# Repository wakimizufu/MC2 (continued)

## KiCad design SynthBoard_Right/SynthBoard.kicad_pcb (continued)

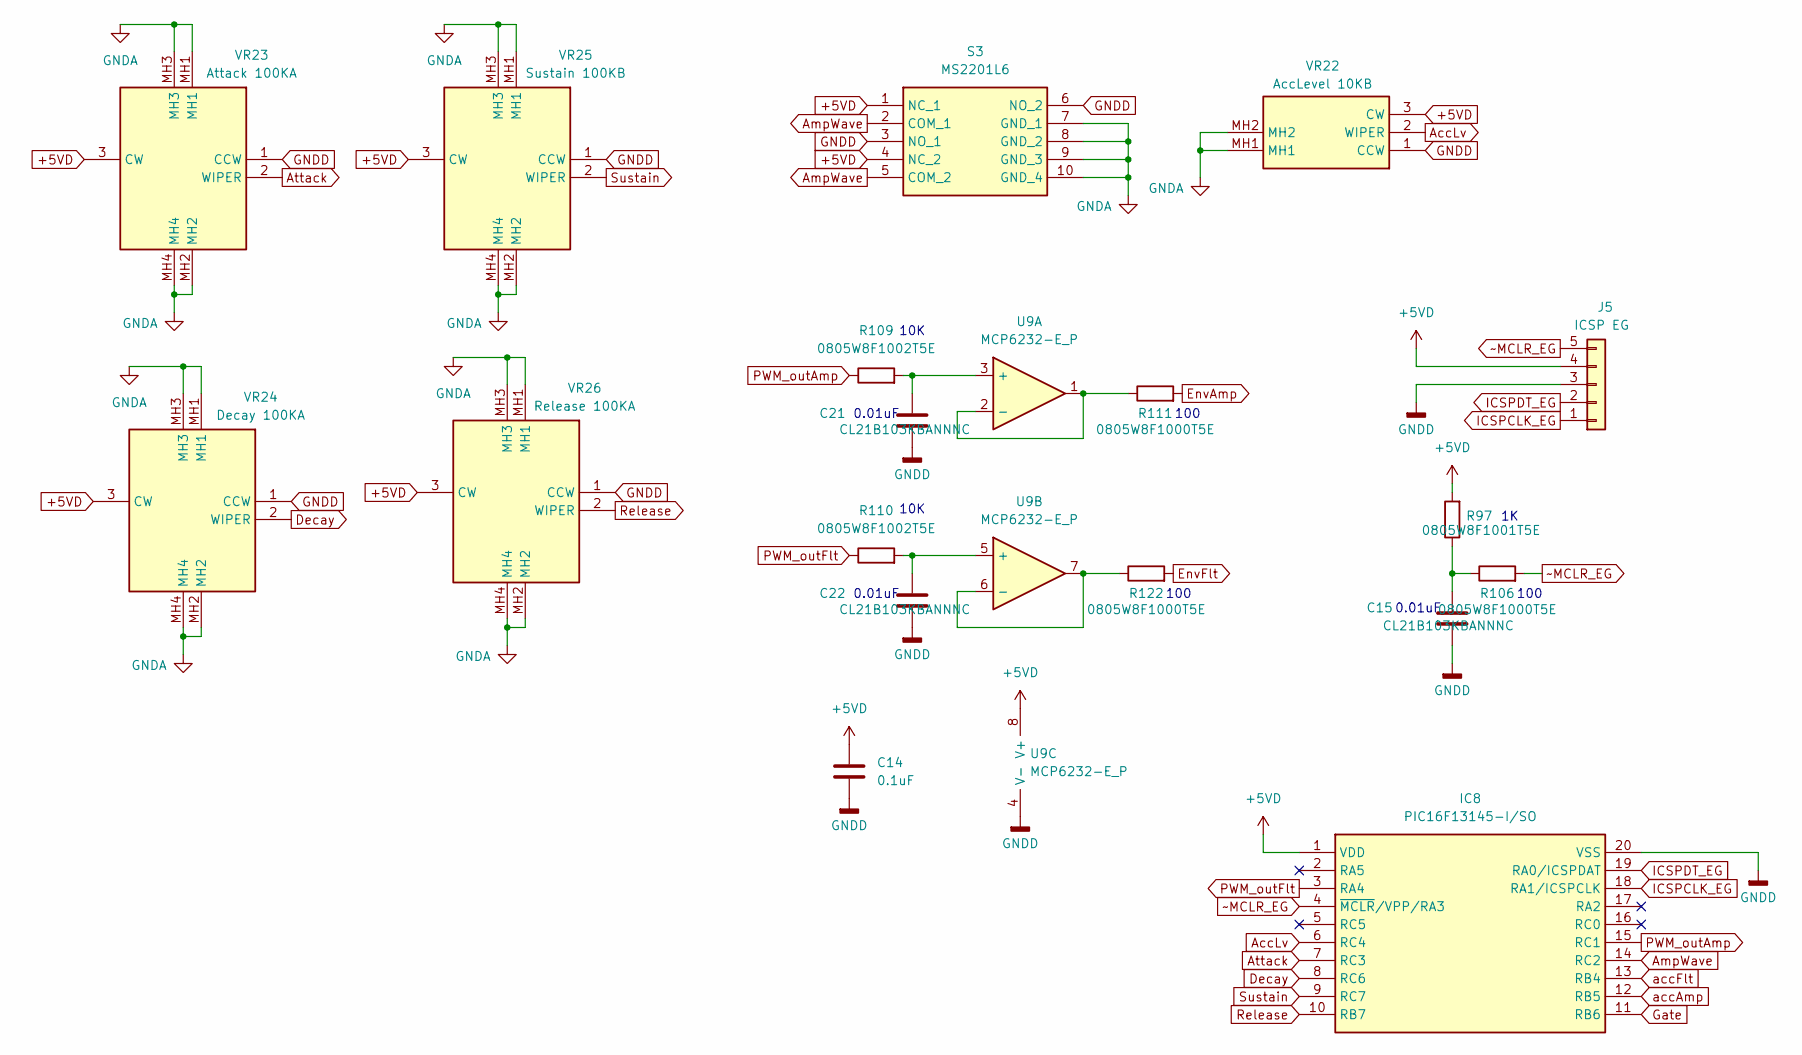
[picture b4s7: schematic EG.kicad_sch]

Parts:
C14: 0.1uF; C_0805_2012Metric_Pad1.18x1.45mm_HandSolder
C15, C21, C22: CL21B103KBANNNC; C_0805_2012Metric_Pad1.18x1.45mm_HandSolder
IC8: PIC16F13145-I/SO; SOIC-20W_7.5x12.8mm_P1.27mm; Manufacturer_Part_Number PIC16F13145-I/P; Mouser Part Number 579-PIC16F13145-I/P
J5: ICSP EG; PinHeader_1x05_P2.54mm_Vertical
R97: 0805W8F1001T5E; R_0805_2012Metric_Pad1.20x1.40mm_HandSolder
R106, R111, R122: 0805W8F1000T5E; R_0805_2012Metric_Pad1.20x1.40mm_HandSolder
R109, R110: 0805W8F1002T5E; R_0805_2012Metric_Pad1.20x1.40mm_HandSolder
S3: MS2201L6; Manufacturer_Part_Number MS2201L6
U9: MCP6232-E_P; SOIC-8_3.9x4.9mm_P1.27mm
VR22: AccLevel 10KB; RK09D117000B; Manufacturer_Part_Number RK09D117000B; Mouser Part Number 688-RK09D117000B
VR23: Attack 100KA; PTA20432010CIB104; Manufacturer_Part_Number PTA2043-2010CIB104; Mouser Part Number 652-PTA2432010CIB104
VR24: Decay 100KA; PTA20432010CIB104; Manufacturer_Part_Number PTA2043-2010CIB104; Mouser Part Number 652-PTA2432010CIB104
VR25: Sustain 100KB; PTA20432010CIB104; Manufacturer_Part_Number PTA2043-2010CIB104; Mouser Part Number 652-PTA2432010CIB104
VR26: Release 100KA; PTA20432010CIB104; Manufacturer_Part_Number PTA2043-2010CIB104; Mouser Part Number 652-PTA2432010CIB104

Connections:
+5VD: C14.1, IC8.1 (VDD), J5.4, R97.2, S3.1 (NC_1), S3.4 (NC_2), U9.8 (V+), VR22.3 (CW), VR23.3 (CW), VR24.3 (CW), VR25.3 (CW), VR26.3 (CW); also elsewhere on the board
AccLv: IC8.6 (RC4), VR22.2 (WIPER)
AmpWave: IC8.14 (RC2), S3.2 (COM_1), S3.5 (COM_2)
Attack: IC8.7 (RC3), VR23.2 (WIPER)
Decay: IC8.8 (RC6), VR24.2 (WIPER)
EnvAmp: R111.2; also elsewhere on the board
EnvFlt: R122.2; also elsewhere on the board
GNDA: S3.7 (GND_1), S3.8 (GND_2), S3.9 (GND_3), S3.10 (GND_4), VR22.MH1, VR22.MH2, VR23.MH1, VR23.MH2, VR23.MH3, VR23.MH4, VR24.MH1, VR24.MH2, VR24.MH3, VR24.MH4, VR25.MH1, VR25.MH2, VR25.MH3, VR25.MH4, VR26.MH1, VR26.MH2, VR26.MH3, VR26.MH4; also elsewhere on the board
GNDD: C14.2, C15.2, C21.2, C22.2, IC8.20 (VSS), J5.3, S3.3 (NO_1), S3.6 (NO_2), U9.4 (V-), VR22.1 (CCW), VR23.1 (CCW), VR24.1 (CCW), VR25.1 (CCW), VR26.1 (CCW); also elsewhere on the board
Gate: IC8.11 (RB6); also elsewhere on the board
ICSPCLK_EG: IC8.18 (RA1/ICSPCLK), J5.1
ICSPDT_EG: IC8.19 (RA0/ICSPDAT), J5.2
unnamed: C15.1, R97.1, R106.1
unnamed: C21.1, R109.2, U9.3 (+)
unnamed: R111.1, U9.1, U9.2 (-)
unnamed: C22.1, R110.2, U9.5 (+)
unnamed: R122.1, U9.6 (-), U9.7
PWM_outAmp: IC8.15 (RC1), R109.1
PWM_outFlt: IC8.3 (RA4), R110.1
Release: IC8.10 (RB7), VR26.2 (WIPER)
Sustain: IC8.9 (RC7), VR25.2 (WIPER)
accAmp: IC8.12 (RB5); also elsewhere on the board
accFlt: IC8.13 (RB4); also elsewhere on the board
~MCLR_EG: IC8.4 (~MCLR/VPP/RA3), J5.5, R106.2

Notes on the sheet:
0.01uF
100
10K

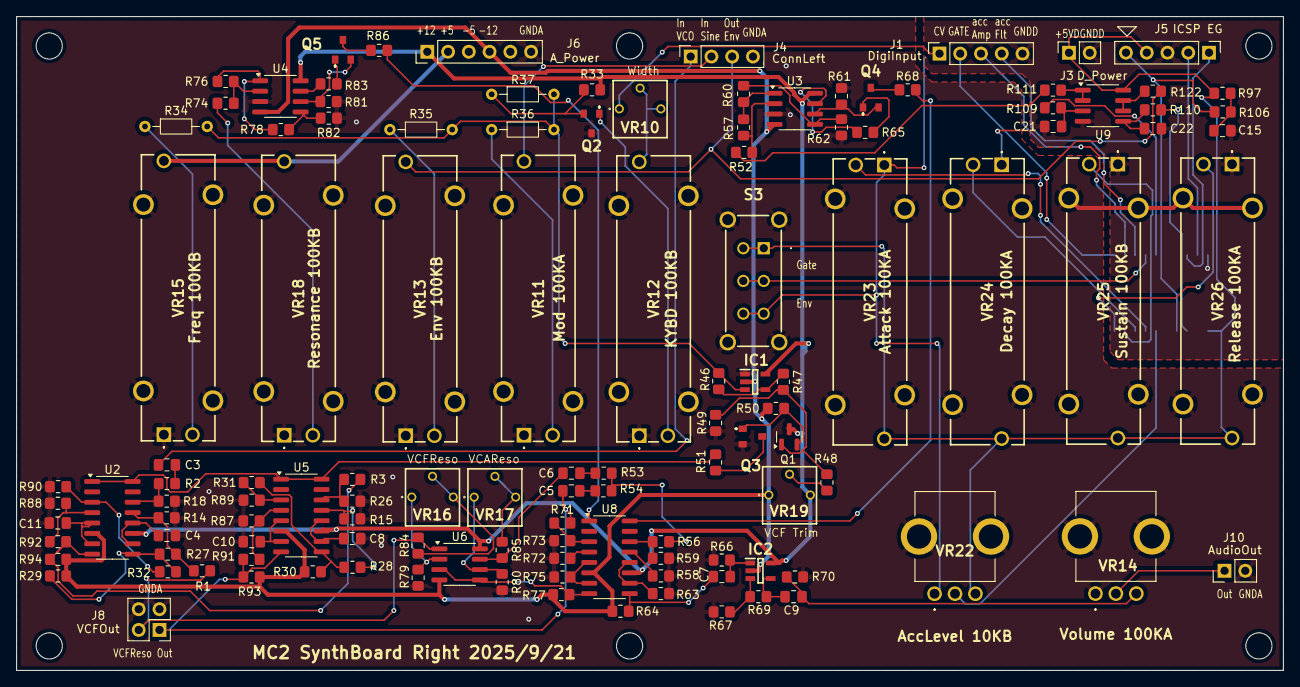
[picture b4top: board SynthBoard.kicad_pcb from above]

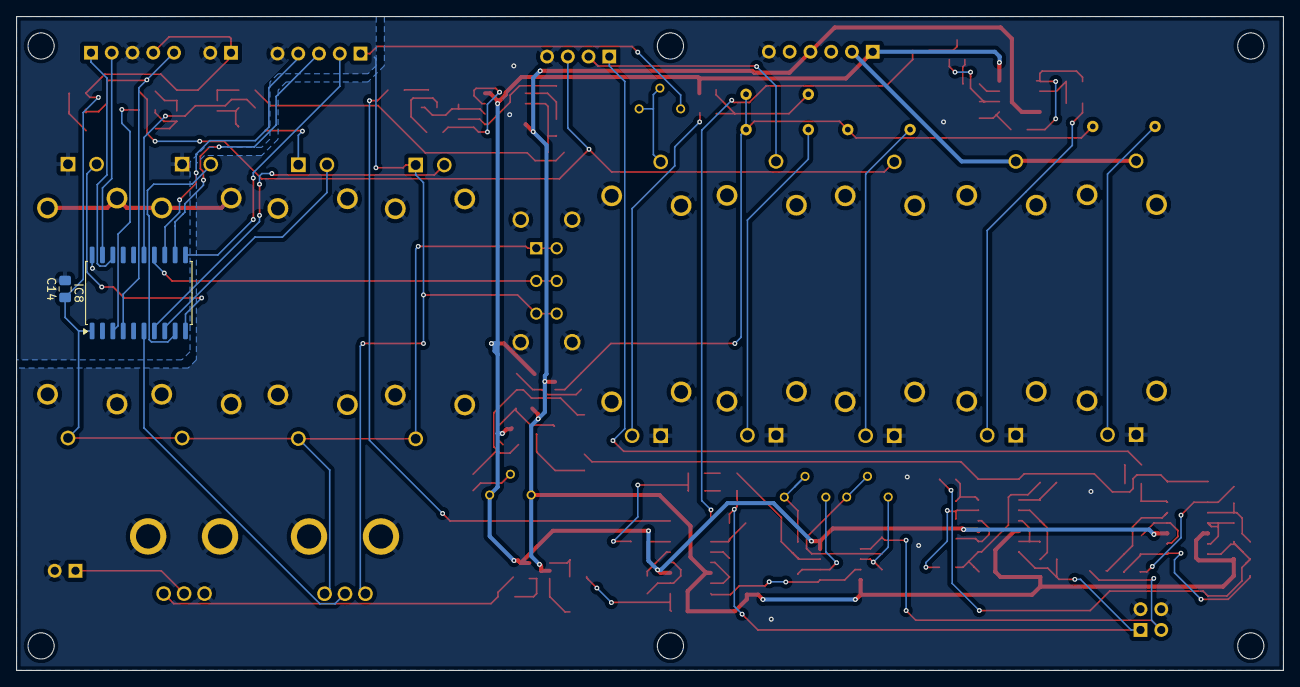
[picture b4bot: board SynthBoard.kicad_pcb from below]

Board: 2 copper layers, 155.0 x 80.0 mm, 123 parts (2 on the bottom side), 99 nets.

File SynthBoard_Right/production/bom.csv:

Designator,Footprint,Quantity,Value,LCSC Part #
"C10, C11, C4, C8",0805,4,ECH-U1H221JX5,
C14,0805,1,0.1uF,
"C15, C21, C22",0805,3,CL21B103KBANNNC,
"C3, C5, C6",0805,3,CL21A106KAYNNNE,
"C7, C9",0805,2,CL21B105KBFNNNE,
"IC1, IC2",SOT95P282X145-5N,2,AS321KTR-G1,
IC8,SOIC-20W_7.5x12.8mm_P1.27mm,1,PIC16F13145-I/SO,
J1,PinSocket_1x05_P2.54mm_Vertical,1,DigiInput,
J10,PinHeader_1x02_P2.54mm_Vertical,1,AudioOut,
J3,PinSocket_1x02_P2.54mm_Vertical,1,D_Power,
J4,PinSocket_1x04_P2.54mm_Vertical,1,ConnLeft,
J5,PinHeader_1x05_P2.54mm_Vertical,1,ICSP EG,
J6,PinHeader_1x06_P2.54mm_Vertical,1,A_Power,
J8,PinSocket_2x02_P2.54mm_Vertical,1,VCFOut,
Q1,SOT-23,1,SS8050(RANGE:200-350),
"Q2, Q3, Q4, Q5",1SS294LFT,4,2SA1162-GR_F_,
"R1, R2, R3, R31, R32, R50, R52, R57, R66, R70, R74",0805,11,0805W8F1003T5E,
"R106, R111, R122",0805,3,0805W8F1000T5E,
"R109, R110, R29, R30, R46, R51, R54, R56, R60, R63, R67, R68, R71, R75, R78, R79, R80, R84, R93, R94",0805,20,0805W8F1002T5E,
"R14, R15, R18, R26, R58, R59, R72, R73, R87, R88, R89, R90",0805,12,0805W8F5600T5E,
"R27, R28, R91, R92",0805,4,0805W8F6802T5E,
R33,0805,1,0805W8F3302T5E,
R34,R_Axial_DIN0204_L3.6mm_D1.6mm_P7.62mm_Horizontal,1,20K,
R35,R_Axial_DIN0204_L3.6mm_D1.6mm_P7.62mm_Horizontal,1,56K,
R36,R_Axial_DIN0204_L3.6mm_D1.6mm_P7.62mm_Horizontal,1,39K,
R37,R_Axial_DIN0204_L3.6mm_D1.6mm_P7.62mm_Horizontal,1,150K,
R47,0805,1,0805W8F2702T5E,
"R48, R53, R69",0805,3,0805W8F4702T5E,
"R49, R61, R62, R65, R81, R82, R83, R85, R97",0805,9,0805W8F1001T5E,
"R64, R77, R86",0805,3,0805W8F5101T5E,
R76,0805,1,0805W8F2003T5E,
S3,MS2201L6,1,MS2201L6,
"U2, U5, U8",SOIC-16_3.9x9.9mm_P1.27mm,3,LM13700,
"U3, U4, U6",SOIC-8_3.9x4.9mm_P1.27mm,3,TL072CDT,
U9,SOIC-8_3.9x4.9mm_P1.27mm,1,MCP6232-E_P,
VR10,3362P_1,1,3362P-1-503LF,
VR11,PTA20432010CIB104,1,Mod 100KA,
VR12,PTA20432010CIB104,1,KYBD 100KB,
VR13,PTA20432010CIB104,1,Env 100KB,
VR14,RK09D117000B,1,Volume 100KA,
VR15,PTA20432010CIB104,1,Freq 100KB,
"VR16, VR17",3362P_1,2,3362P-1-103LF,
VR18,PTA20432010CIB104,1,Resonance 100KB,
VR19,3362P_1,1,3362P-1-104LF,
VR22,RK09D117000B,1,AccLevel 10KB,
VR23,PTA20432010CIB104,1,Attack 100KA,
VR24,PTA20432010CIB104,1,Decay 100KA,
VR25,PTA20432010CIB104,1,Sustain 100KB,
VR26,PTA20432010CIB104,1,Release 100KA,

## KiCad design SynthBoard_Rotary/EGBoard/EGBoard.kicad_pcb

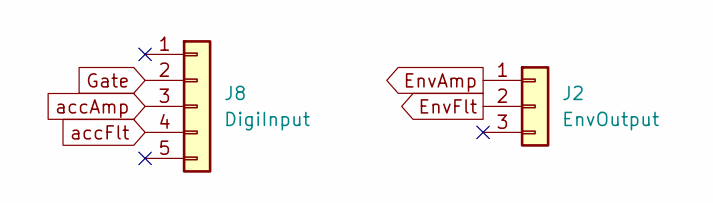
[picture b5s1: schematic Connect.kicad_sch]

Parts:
J2: EnvOutput; PinSocket_1x03_P2.54mm_Vertical
J8: DigiInput; PinSocket_1x05_P2.54mm_Vertical

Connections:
EnvAmp: J2.1; also elsewhere on the board
EnvFlt: J2.2; also elsewhere on the board
Gate: J8.2; also elsewhere on the board
accAmp: J8.3; also elsewhere on the board
accFlt: J8.4; also elsewhere on the board

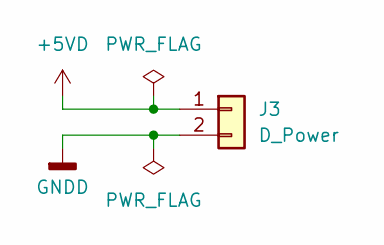
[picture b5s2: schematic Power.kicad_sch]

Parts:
J3: D_Power; PinSocket_1x02_P2.54mm_Vertical

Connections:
+5VD: J3.1; also elsewhere on the board
GNDD: J3.2; also elsewhere on the board

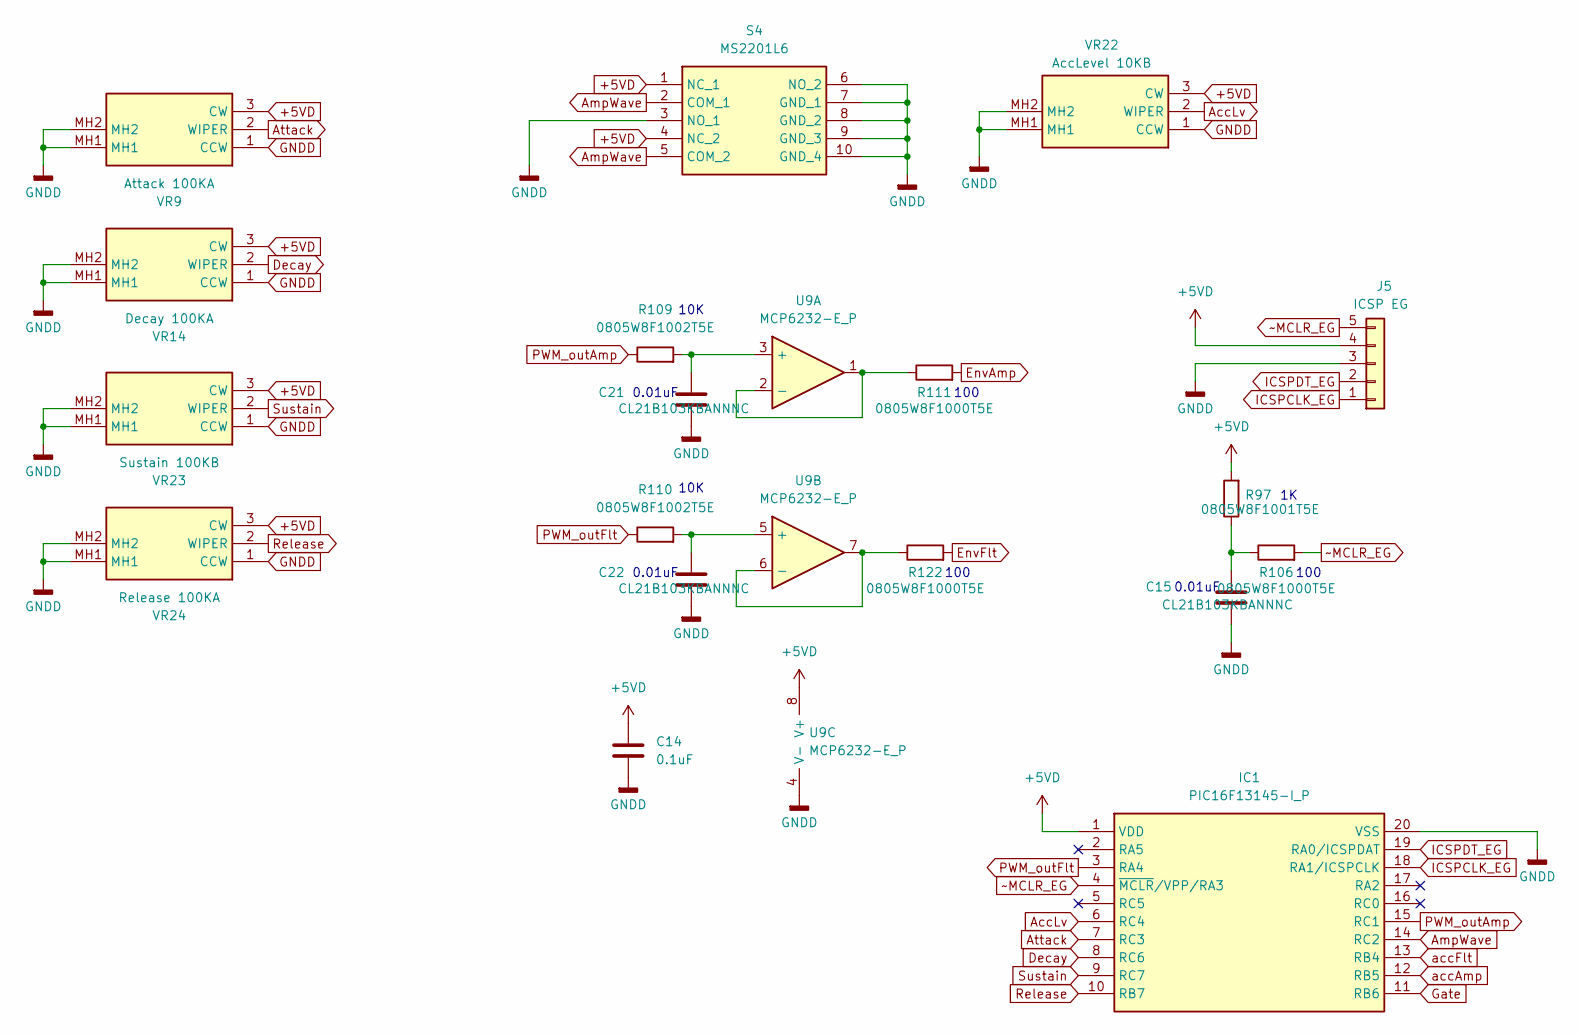
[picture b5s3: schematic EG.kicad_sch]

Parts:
C14: 0.1uF; C_0805_2012Metric_Pad1.18x1.45mm_HandSolder
C15, C21, C22: CL21B103KBANNNC; C_0805_2012Metric_Pad1.18x1.45mm_HandSolder
IC1: PIC16F13145-I_P; DIP794W56P254L2591H533Q20N; Manufacturer_Part_Number PIC16F13145-I/P; Mouser Part Number 579-PIC16F13145-I/P
J5: ICSP EG; PinHeader_1x05_P2.54mm_Vertical
R97: 0805W8F1001T5E; R_0805_2012Metric_Pad1.20x1.40mm_HandSolder
R106, R111, R122: 0805W8F1000T5E; R_0805_2012Metric_Pad1.20x1.40mm_HandSolder
R109, R110: 0805W8F1002T5E; R_0805_2012Metric_Pad1.20x1.40mm_HandSolder
S4: MS2201L6; Manufacturer_Part_Number MS2201L6
U9: MCP6232-E_P; SOIC-8_3.9x4.9mm_P1.27mm
VR9: Attack 100KA; RK09D117000B; Manufacturer_Part_Number RK09D117000B; Mouser Part Number 688-RK09D117000B
VR14: Decay 100KA; RK09D117000B; Manufacturer_Part_Number RK09D117000B; Mouser Part Number 688-RK09D117000B
VR22: AccLevel 10KB; RK09D117000B; Manufacturer_Part_Number RK09D117000B; Mouser Part Number 688-RK09D117000B
VR23: Sustain 100KB; RK09D117000B; Manufacturer_Part_Number RK09D117000B; Mouser Part Number 688-RK09D117000B
VR24: Release 100KA; RK09D117000B; Manufacturer_Part_Number RK09D117000B; Mouser Part Number 688-RK09D117000B

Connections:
+5VD: C14.1, IC1.1 (VDD), J5.4, R97.2, S4.1 (NC_1), S4.4 (NC_2), U9.8 (V+), VR9.3 (CW), VR14.3 (CW), VR22.3 (CW), VR23.3 (CW), VR24.3 (CW); also elsewhere on the board
AccLv: IC1.6 (RC4), VR22.2 (WIPER)
AmpWave: IC1.14 (RC2), S4.2 (COM_1), S4.5 (COM_2)
Attack: IC1.7 (RC3), VR9.2 (WIPER)
Decay: IC1.8 (RC6), VR14.2 (WIPER)
EnvAmp: R111.2; also elsewhere on the board
EnvFlt: R122.2; also elsewhere on the board
GNDD: C14.2, C15.2, C21.2, C22.2, IC1.20 (VSS), J5.3, S4.3 (NO_1), S4.6 (NO_2), S4.7 (GND_1), S4.8 (GND_2), S4.9 (GND_3), S4.10 (GND_4), U9.4 (V-), VR9.1 (CCW), VR9.MH1, VR9.MH2, VR14.1 (CCW), VR14.MH1, VR14.MH2, VR22.1 (CCW), VR22.MH1, VR22.MH2, VR23.1 (CCW), VR23.MH1, VR23.MH2, VR24.1 (CCW), VR24.MH1, VR24.MH2; also elsewhere on the board
Gate: IC1.11 (RB6); also elsewhere on the board
ICSPCLK_EG: IC1.18 (RA1/ICSPCLK), J5.1
ICSPDT_EG: IC1.19 (RA0/ICSPDAT), J5.2
unnamed: C15.1, R97.1, R106.1
unnamed: C21.1, R109.2, U9.3 (+)
unnamed: R111.1, U9.1, U9.2 (-)
unnamed: C22.1, R110.2, U9.5 (+)
unnamed: R122.1, U9.6 (-), U9.7
PWM_outAmp: IC1.15 (RC1), R109.1
PWM_outFlt: IC1.3 (RA4), R110.1
Release: IC1.10 (RB7), VR24.2 (WIPER)
Sustain: IC1.9 (RC7), VR23.2 (WIPER)
accAmp: IC1.12 (RB5); also elsewhere on the board
accFlt: IC1.13 (RB4); also elsewhere on the board
~MCLR_EG: IC1.4 (~MCLR/VPP/RA3), J5.5, R106.2

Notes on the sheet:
0.01uF
100
10K

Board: 2 copper layers, 22 parts (0 on the bottom side), 23 nets, no tracks yet.

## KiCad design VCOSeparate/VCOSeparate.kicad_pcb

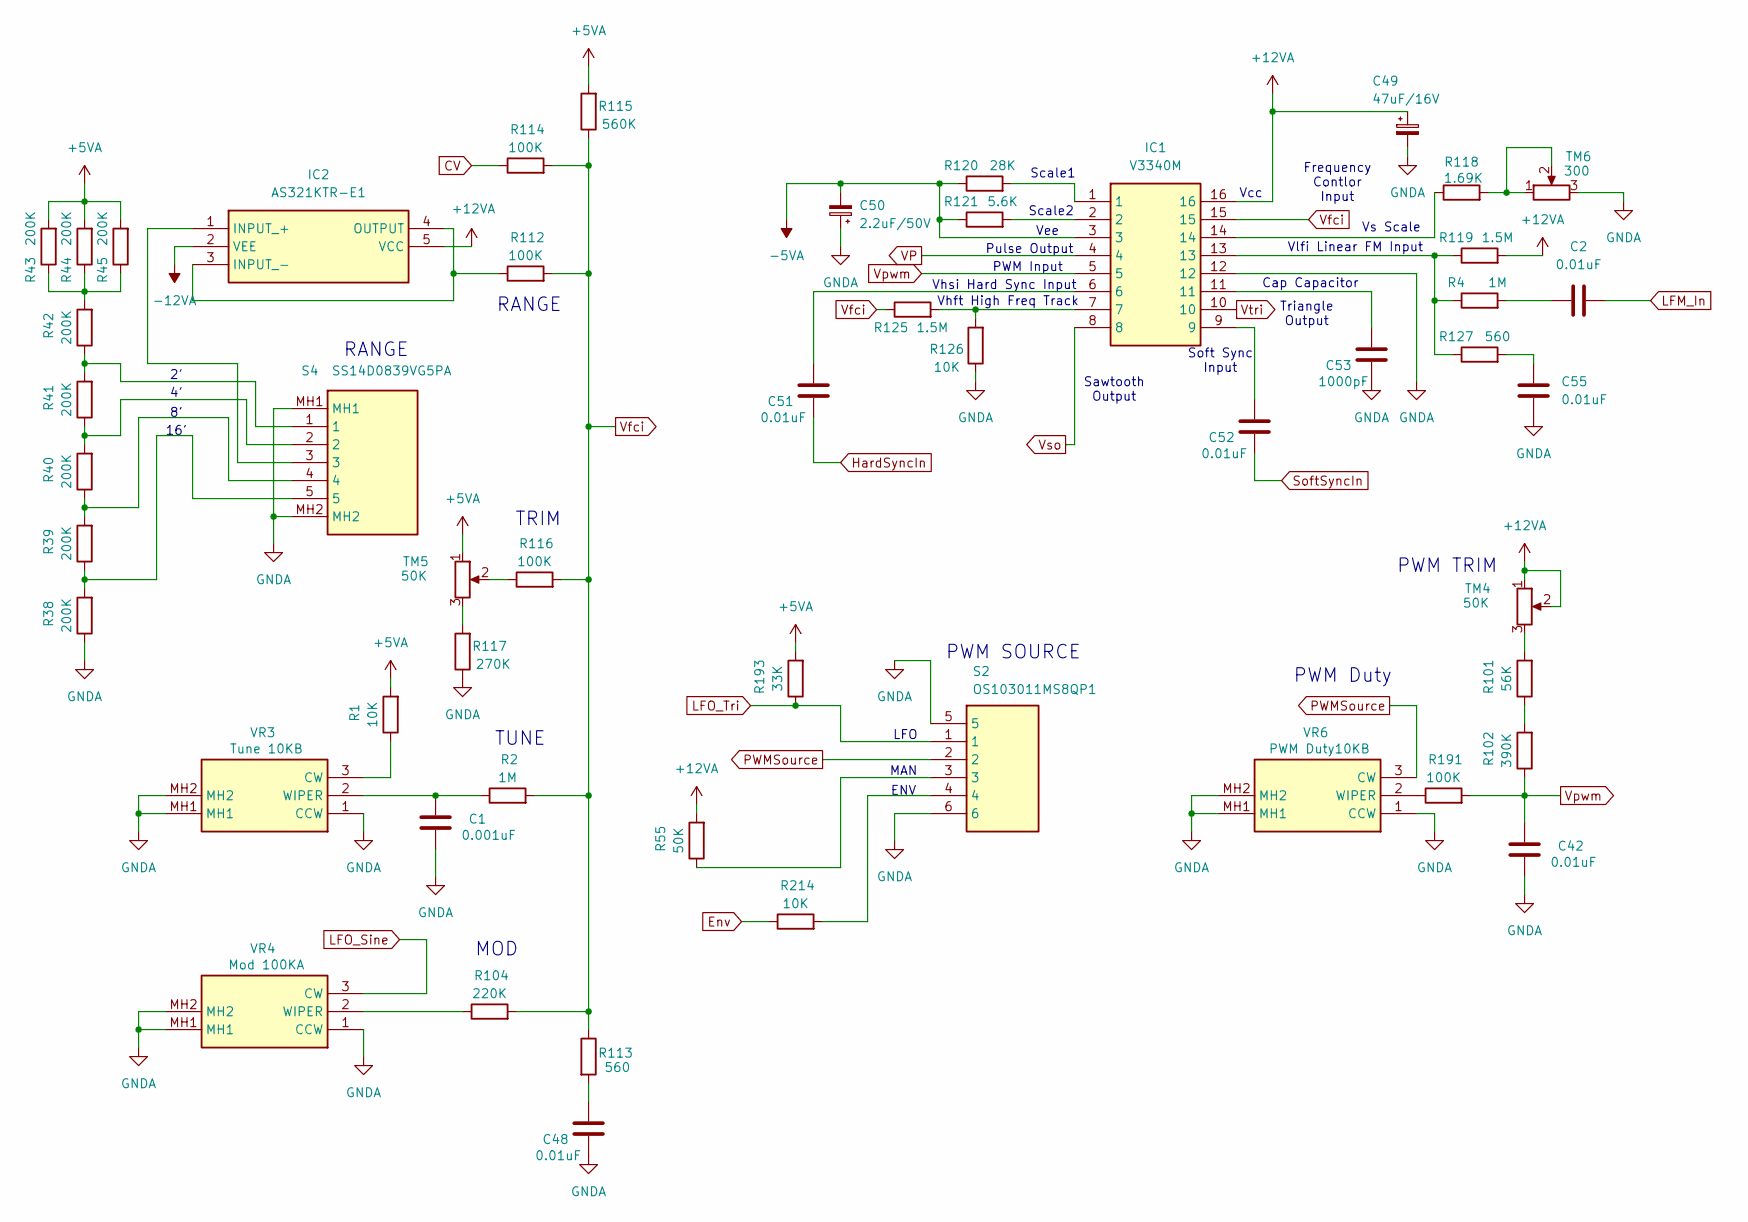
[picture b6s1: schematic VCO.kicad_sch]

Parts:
C1: 0.001uF; C_Disc_D5.0mm_W2.5mm_P2.50mm
C2, C42, C48, C51, C52, C55: 0.01uF; C_Disc_D5.0mm_W2.5mm_P2.50mm
C49: 47uF/16V; CP_Radial_D5.0mm_P2.50mm
C50: 2.2uF/50V; CP_Radial_D5.0mm_P2.50mm
C53: 1000pF; C_Disc_D5.0mm_W2.5mm_P2.50mm
IC1: V3340M; DIP794W56P260L1905H432Q16N; Manufacturer_Part_Number V3340M
IC2: AS321KTR-E1; SOT95P282X145-5N; Manufacturer_Part_Number AS321KTR-E1; Mouser Part Number 621-AS321KTR-E1
R1, R126, R214: 10K; R_Axial_DIN0207_L6.3mm_D2.5mm_P2.54mm_Vertical
R2, R4: 1M; R_Axial_DIN0207_L6.3mm_D2.5mm_P2.54mm_Vertical
R38, R39, R40, R41, R42, R43, R44, R45: 200K; R_Axial_DIN0207_L6.3mm_D2.5mm_P2.54mm_Vertical
R55: 50K; R_Axial_DIN0207_L6.3mm_D2.5mm_P2.54mm_Vertical
R101: 56K; R_Axial_DIN0207_L6.3mm_D2.5mm_P2.54mm_Vertical
R102: 390K; R_Axial_DIN0207_L6.3mm_D2.5mm_P2.54mm_Vertical
R104: 220K; R_Axial_DIN0207_L6.3mm_D2.5mm_P2.54mm_Vertical
R112, R114, R116, R191: 100K; R_Axial_DIN0207_L6.3mm_D2.5mm_P2.54mm_Vertical
R113, R127: 560; R_Axial_DIN0207_L6.3mm_D2.5mm_P2.54mm_Vertical
R115: 560K; R_Axial_DIN0207_L6.3mm_D2.5mm_P2.54mm_Vertical
R117: 270K; R_Axial_DIN0207_L6.3mm_D2.5mm_P2.54mm_Vertical
R118: 1.69K; R_Axial_DIN0207_L6.3mm_D2.5mm_P2.54mm_Vertical
R119, R125: 1.5M; R_Axial_DIN0207_L6.3mm_D2.5mm_P2.54mm_Vertical
R120: 28K; R_Axial_DIN0207_L6.3mm_D2.5mm_P2.54mm_Vertical
R121: 5.6K; R_Axial_DIN0207_L6.3mm_D2.5mm_P2.54mm_Vertical
R193: 33K; R_Axial_DIN0207_L6.3mm_D2.5mm_P2.54mm_Vertical
S2: OS103011MS8QP1; Manufacturer_Part_Number OS103011MS8QP1; Mouser Part Number 611-OS103011MS8QP1
S4: SS14D0839VG5PA; Manufacturer_Part_Number SS14D0839VG5PA; Mouser Part Number 611-SS-14D0839-VG5PA
TM4, TM5: 50K; Potentiometer_Bourns_3386P_Vertical
TM6: 300; Potentiometer_Bourns_3386P_Vertical
VR3: Tune 10KB; RK09D117000B; Manufacturer_Part_Number RK09D117000B; Mouser Part Number 688-RK09D117000B
VR4: Mod 100KA; RK09D117000B; Manufacturer_Part_Number RK09D117000B; Mouser Part Number 688-RK09D117000B
VR6: PWM Duty10KB; RK09D117000B; Manufacturer_Part_Number RK09D117000B; Mouser Part Number 688-RK09D117000B

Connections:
+5VA: R1.2, R43.2, R44.2, R45.2, R115.2, R193.2, TM5.1; also elsewhere on the board
+12VA: C49.1, IC1.16, IC2.5 (VCC), R55.2, R119.2, TM4.1, TM4.2; also elsewhere on the board
-5VA: C50.2, IC1.3, R120.1, R121.1; also elsewhere on the board
-12VA: IC2.2 (VEE); also elsewhere on the board
CV: R114.1; also elsewhere on the board
Env: R214.1; also elsewhere on the board
GNDA: C1.1, C42.1, C48.1, C49.2, C50.1, C53.1, C55.1, IC1.12, R38.1, R117.1, R126.1, S2.5, S2.6, S4.MH1, S4.MH2, TM6.3, VR3.1 (CCW), VR3.MH1, VR3.MH2, VR4.1 (CCW), VR4.MH1, VR4.MH2, VR6.1 (CCW), VR6.MH1, VR6.MH2; also elsewhere on the board
HardSyncIn: C51.1; also elsewhere on the board
LFM_In: C2.1; also elsewhere on the board
LFO_Sine: VR4.3 (CW); also elsewhere on the board
LFO_Tri: R193.1, S2.1; also elsewhere on the board
unnamed: C2.2, R4.2
unnamed: C48.2, R113.2
unnamed: C51.2, IC1.6
unnamed: C52.2, IC1.9
unnamed: C53.2, IC1.11
unnamed: C55.2, R127.2
unnamed: IC1.1, R120.2
unnamed: IC1.2, R121.2
unnamed: IC1.7, R125.2, R126.2
unnamed: IC1.13, R4.1, R119.1, R127.1
unnamed: IC1.14, R118.1
unnamed: IC2.1 (INPUT_+), S4.3
unnamed: IC2.3 (INPUT_-), IC2.4 (OUTPUT), R112.1
unnamed: R38.2, R39.1, S4.5
unnamed: R39.2, R40.1, S4.4
unnamed: R40.2, R41.1, S4.2
unnamed: R41.2, R42.1, S4.1
unnamed: R42.2, R43.1, R44.1, R45.1
unnamed: R55.1, S2.3
unnamed: R101.1, R102.2
unnamed: R101.2, TM4.3
unnamed: R116.1, TM5.2
unnamed: R117.2, TM5.3
unnamed: R118.2, TM6.1, TM6.2
unnamed: R214.2, S2.4
unnamed: R1.1, VR3.3 (CW)
unnamed: C1.2, R2.1, VR3.2 (WIPER)
unnamed: R104.1, VR4.2 (WIPER)
unnamed: R191.1, VR6.2 (WIPER)
PWMSource: S2.2, VR6.3 (CW)
SoftSyncIn: C52.1; also elsewhere on the board
VP: IC1.4; also elsewhere on the board
Vfci: IC1.15, R2.2, R104.2, R112.2, R113.1, R114.2, R115.1, R116.2, R125.1
Vpwm: C42.2, IC1.5, R102.1, R191.2
Vso: IC1.8; also elsewhere on the board
Vtri: IC1.10; also elsewhere on the board

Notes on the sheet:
Vhft High Freq Track
LFO
TRIM
MOD
Vee
MAN
Sawtooth Output
PWM Input
RANGE
Vcc
PWM SOURCE
Vhsi Hard Sync Input
PWM TRIM
Vlfi Linear FM Input
16'
Pulse Output
Vs Scale
Scale1
Scale2
Triangle Output
Cap Capacitor
PWM Duty
Frequency Contlor Input
Soft Sync Input
TUNE
ENV

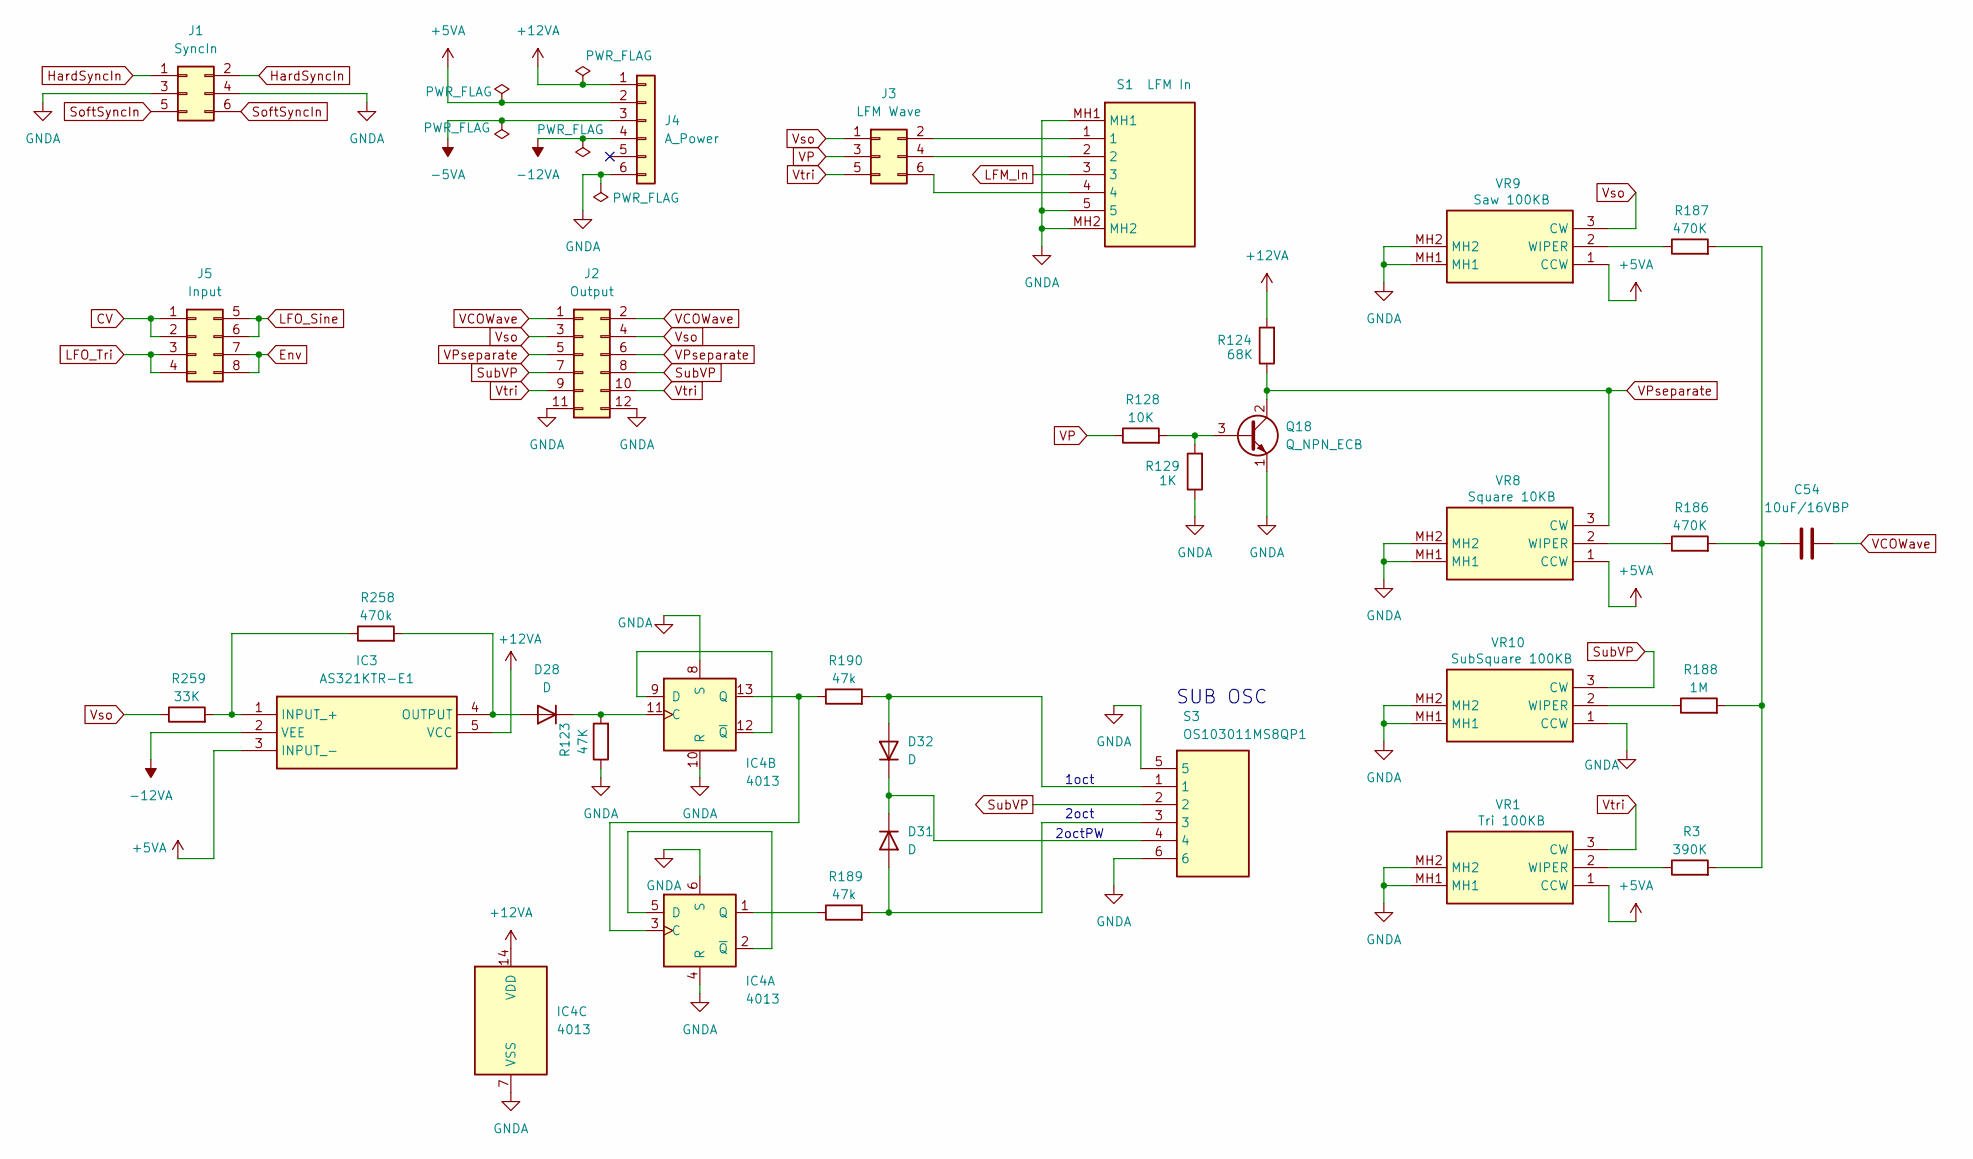
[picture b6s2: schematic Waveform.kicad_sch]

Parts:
C54: 10uF/16VBP; C_Radial_D6.3mm_H7.0mm_P2.50mm
D28, D31, D32: D; D_DO-15_P2.54mm_Vertical_AnodeUp
IC3: AS321KTR-E1; SOT95P282X145-5N; Manufacturer_Part_Number AS321KTR-E1; Mouser Part Number 621-AS321KTR-E1
IC4: 4013; DIP-14_W7.62mm_LongPads
J1: SyncIn; PinSocket_2x03_P2.54mm_Vertical
J2: Output; PinSocket_2x06_P2.54mm_Vertical
J3: LFM Wave; PinSocket_2x03_P2.54mm_Vertical
J4: A_Power; PinHeader_1x06_P2.54mm_Vertical
J5: Input; PinSocket_2x04_P2.54mm_Vertical
Q18: Q_NPN_ECB; TO-92_HandSolder
R3: 390K; R_Axial_DIN0207_L6.3mm_D2.5mm_P2.54mm_Vertical
R123: 47K; R_Axial_DIN0207_L6.3mm_D2.5mm_P2.54mm_Vertical
R124: 68K; R_Axial_DIN0207_L6.3mm_D2.5mm_P2.54mm_Vertical
R128: 10K; R_Axial_DIN0207_L6.3mm_D2.5mm_P2.54mm_Vertical
R129: 1K; R_Axial_DIN0207_L6.3mm_D2.5mm_P2.54mm_Vertical
R186, R187: 470K; R_Axial_DIN0207_L6.3mm_D2.5mm_P2.54mm_Vertical
R188: 1M; R_Axial_DIN0207_L6.3mm_D2.5mm_P2.54mm_Vertical
R189, R190: 47k; R_Axial_DIN0207_L6.3mm_D2.5mm_P2.54mm_Vertical
R258: 470k; R_Axial_DIN0207_L6.3mm_D2.5mm_P2.54mm_Vertical
R259: 33K; R_Axial_DIN0207_L6.3mm_D2.5mm_P2.54mm_Vertical
S1: LFM In; SS14D0839VG5PA; Manufacturer_Part_Number SS14D0839VG5PA; Mouser Part Number 611-SS-14D0839-VG5PA
S3: OS103011MS8QP1; Manufacturer_Part_Number OS103011MS8QP1; Mouser Part Number 611-OS103011MS8QP1
VR1: Tri 100KB; RK09D117000B; Manufacturer_Part_Number RK09D117000B; Mouser Part Number 688-RK09D117000B
VR8: Square 10KB; RK09D117000B; Manufacturer_Part_Number RK09D117000B; Mouser Part Number 688-RK09D117000B
VR9: Saw 100KB; RK09D117000B; Manufacturer_Part_Number RK09D117000B; Mouser Part Number 688-RK09D117000B
VR10: SubSquare 100KB; RK09D117000B; Manufacturer_Part_Number RK09D117000B; Mouser Part Number 688-RK09D117000B

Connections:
+5VA: IC3.3 (INPUT_-), J4.2, VR1.1 (CCW), VR8.1 (CCW), VR9.1 (CCW); also elsewhere on the board
+12VA: IC3.5 (VCC), IC4.14 (VDD), J4.1, R124.2; also elsewhere on the board
-5VA: J4.3; also elsewhere on the board
-12VA: IC3.2 (VEE), J4.4; also elsewhere on the board
CV: J5.1, J5.2; also elsewhere on the board
Env: J5.7, J5.8; also elsewhere on the board
GNDA: IC4.4 (R), IC4.6 (S), IC4.7 (VSS), IC4.8 (S), IC4.10 (R), J1.3, J1.4, J2.11, J2.12, J4.6, Q18.1 (E), R123.1, R129.1, S1.5, S1.MH1, S1.MH2, S3.5, S3.6, VR1.MH1, VR1.MH2, VR8.MH1, VR8.MH2, VR9.MH1, VR9.MH2, VR10.1 (CCW), VR10.MH1, VR10.MH2; also elsewhere on the board
HardSyncIn: J1.1, J1.2; also elsewhere on the board
LFM_In: S1.3; also elsewhere on the board
LFO_Sine: J5.5, J5.6; also elsewhere on the board
LFO_Tri: J5.3, J5.4; also elsewhere on the board
unnamed: C54.1, R3.2, R186.2, R187.2, R188.2
unnamed: D28.2 (A), IC3.4 (OUTPUT), R258.2
unnamed: D28.1 (K), IC4.11 (C), R123.2
unnamed: D31.2 (A), R189.2, S3.3
unnamed: D31.1 (K), D32.1 (K), S3.4
unnamed: D32.2 (A), R190.2, S3.1
unnamed: IC3.1 (INPUT_+), R258.1, R259.2
unnamed: IC4.3 (C), IC4.13 (Q), R190.1
unnamed: IC4.2 (~Q), IC4.5 (D)
unnamed: IC4.1 (Q), R189.1
unnamed: IC4.9 (D), IC4.12 (~Q)
unnamed: J3.2, S1.1
unnamed: J3.4, S1.2
unnamed: J3.6, S1.4
unnamed: Q18.3 (B), R128.2, R129.2
unnamed: R3.1, VR1.2 (WIPER)
unnamed: R186.1, VR8.2 (WIPER)
unnamed: R187.1, VR9.2 (WIPER)
unnamed: R188.1, VR10.2 (WIPER)
SoftSyncIn: J1.5, J1.6; also elsewhere on the board
SubVP: J2.7, J2.8, S3.2, VR10.3 (CW)
VCOWave: C54.2, J2.1, J2.2
VP: J3.3, R128.1; also elsewhere on the board
VPseparate: J2.5, J2.6, Q18.2 (C), R124.1, VR8.3 (CW)
Vso: J2.3, J2.4, J3.1, R259.1, VR9.3 (CW); also elsewhere on the board
Vtri: J2.9, J2.10, J3.5, VR1.3 (CW); also elsewhere on the board

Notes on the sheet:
1oct
2octPW
SUB OSC
2oct

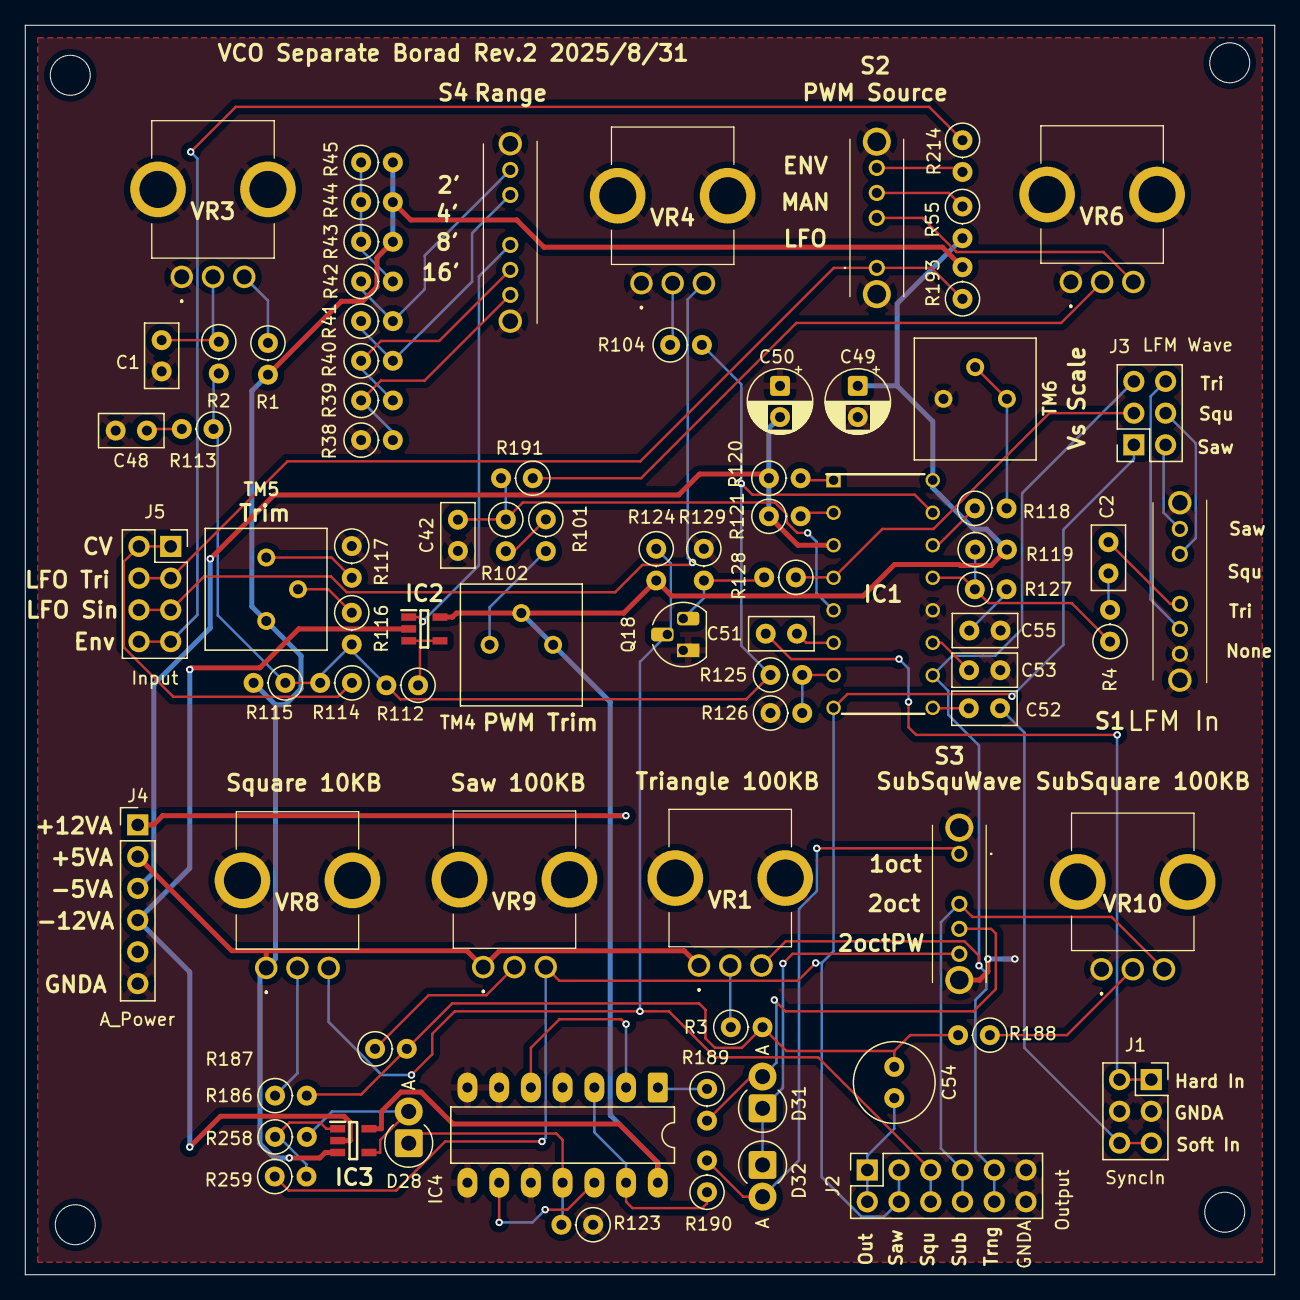
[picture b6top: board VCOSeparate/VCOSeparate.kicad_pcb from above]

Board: 2 copper layers, 100.0 x 100.0 mm, 81 parts (0 on the bottom side), 69 nets.

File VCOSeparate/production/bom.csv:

Designator,Footprint,Quantity,Value,LCSC Part #
C1,C_Disc_D5.0mm_W2.5mm_P2.50mm,1,0.001uF,
"C42, C51, C52, C55",C_Disc_D5.0mm_W2.5mm_P2.50mm,4,0.01uF,
C49,CP_Radial_D5.0mm_P2.50mm,1,47uF/16V,
C50,CP_Radial_D5.0mm_P2.50mm,1,2.2uF/50V,
C53,C_Disc_D5.0mm_W2.5mm_P2.50mm,1,1000pF,
C54,C_Radial_D4.0mm_H7.0mm_P1.50mm,1,10uF/16VBP,
"D28, D31, D32",D_DO-15_P2.54mm_Vertical_AnodeUp,3,D,
IC1,DIP794W56P260L1905H432Q16N,1,V3340M,
"IC2, IC3",SOT95P282X145-5N,2,AS321KTR-E1,
IC4,DIP-14_W7.62mm_LongPads,1,4013,
J3,PinSocket_2x05_P2.54mm_Vertical,1,Output,
J4,PinHeader_1x06_P2.54mm_Vertical,1,A_Power,
J5,PinSocket_2x04_P2.54mm_Vertical,1,Input,
Q18,TO-92_HandSolder,1,Q_NPN_ECB,
"R1, R112, R114, R116, R191",R_Axial_DIN0207_L6.3mm_D2.5mm_P2.54mm_Vertical,5,100K,
R101,R_Axial_DIN0207_L6.3mm_D2.5mm_P2.54mm_Vertical,1,56K,
"R102, R187",R_Axial_DIN0207_L6.3mm_D2.5mm_P2.54mm_Vertical,2,390K,
R104,R_Axial_DIN0207_L6.3mm_D2.5mm_P2.54mm_Vertical,1,220K,
R115,R_Axial_DIN0207_L6.3mm_D2.5mm_P2.54mm_Vertical,1,560K,
R117,R_Axial_DIN0207_L6.3mm_D2.5mm_P2.54mm_Vertical,1,270K,
R118,R_Axial_DIN0207_L6.3mm_D2.5mm_P2.54mm_Vertical,1,1.69K,
"R119, R125",R_Axial_DIN0207_L6.3mm_D2.5mm_P2.54mm_Vertical,2,1.5M,
R120,R_Axial_DIN0207_L6.3mm_D2.5mm_P2.54mm_Vertical,1,28K,
R121,R_Axial_DIN0207_L6.3mm_D2.5mm_P2.54mm_Vertical,1,5.6K,
"R123, R189, R190",R_Axial_DIN0207_L6.3mm_D2.5mm_P2.54mm_Vertical,3,47K,
R124,R_Axial_DIN0207_L6.3mm_D2.5mm_P2.54mm_Vertical,1,68K,
"R126, R128, R214",R_Axial_DIN0207_L6.3mm_D2.5mm_P2.54mm_Vertical,3,10K,
R127,R_Axial_DIN0207_L6.3mm_D2.5mm_P2.54mm_Vertical,1,560,
R129,R_Axial_DIN0207_L6.3mm_D2.5mm_P2.54mm_Vertical,1,1K,
R186,R_Axial_DIN0207_L6.3mm_D2.5mm_P2.54mm_Vertical,1,680K,
"R188, R2",R_Axial_DIN0207_L6.3mm_D2.5mm_P2.54mm_Vertical,2,1M,
"R193, R259",R_Axial_DIN0207_L6.3mm_D2.5mm_P2.54mm_Vertical,2,33K,
R258,R_Axial_DIN0207_L6.3mm_D2.5mm_P2.54mm_Vertical,1,470k,
"R38, R39, R40, R41, R42, R43, R44, R45",R_Axial_DIN0207_L6.3mm_D2.5mm_P2.54mm_Vertical,8,200K,
R55,R_Axial_DIN0207_L6.3mm_D2.5mm_P2.54mm_Vertical,1,50K,
S1,ASLB1470,1,ASLB1470,
"S2, S3",OS103011MS8QP1,2,OS103011MS8QP1,
"TM4, TM5",Potentiometer_Bourns_3386P_Vertical,2,50K,
TM6,Potentiometer_Bourns_3386P_Vertical,1,300,
VR10,RK09D117000B,1,SubSquare 100KB,
VR3,RK09D117000B,1,Tune 10KB,
VR4,RK09D117000B,1,Mod 100KA,
VR6,RK09D117000B,1,PWM Duty10KB,
VR8,RK09D117000B,1,Square 10KB,
VR9,RK09D117000B,1,Saw 100KB,
